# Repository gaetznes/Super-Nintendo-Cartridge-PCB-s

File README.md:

# Super-Nintendo-Cartridge-PCB-s

An assortment of boards I designed while learning how to use Kicad

SNES BASIC 27C160 + CIC (Untested), will update once tested.

SNES 2X 27C160 NOBATTERY (Untested), will update once tested.

SNES 2X 27C160 w BATTERY (Untested), will update once tested.

## Acknowledgements and Thanks goes to:

The Edge connector and edge cut and a fare amount of the net, were sourced from:

Mousebitelabs, https://github.com/MouseBiteLabs/Super-Nintendo-Cartridges/tree/main/Basic%20UV

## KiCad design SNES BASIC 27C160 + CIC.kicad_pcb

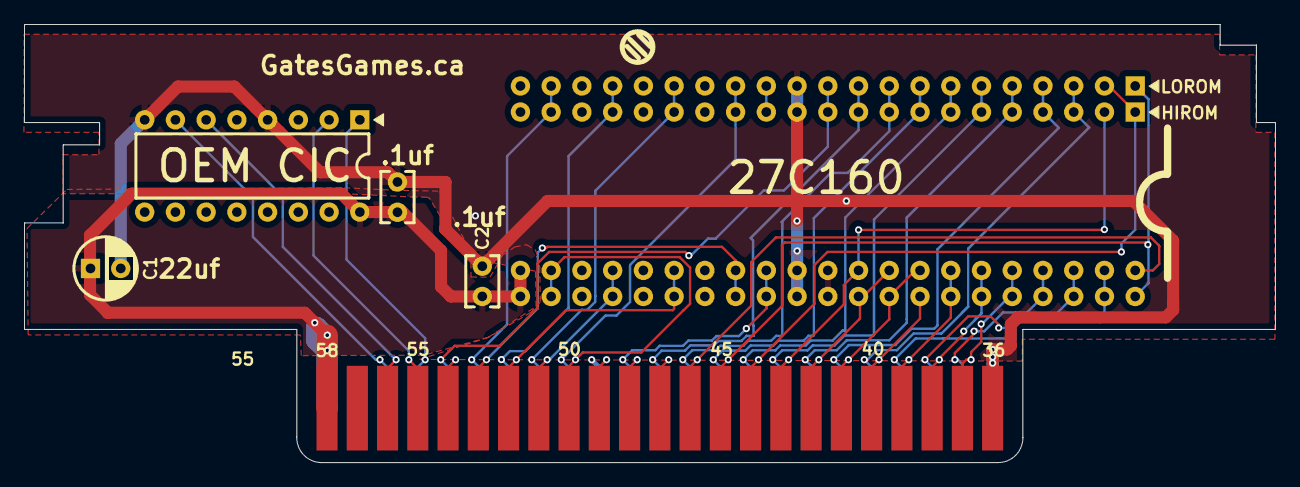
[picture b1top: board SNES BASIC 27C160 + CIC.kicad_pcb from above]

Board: 2 copper layers, 103.4 x 36.2 mm, 7 parts (0 on the bottom side), 38 nets.

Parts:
C1: 22u; CP_Radial_D5.0mm_P2.50mm
C2, C6L: 0.1u; C_THT
P1: SNES_Cartridge; Cart_Edge_SNES_Standard
U2C1: CIC; DIP-16_W7.62mm
U4H1, U4L1: 27C160; DIP-42_W15.24mm

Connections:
+5V: C1.1, C2.1, C6L.1, P1.27 (5V), P1.58 (5V), U2C1.16 (VDD), U4H1.22 (VCC), U4L1.22 (VCC)
/A_{0}: P1.17 (A0), U4H1.30 (D15), U4L1.30 (D15)
/A_{1}: P1.16 (A1), U4H1.10 (A0), U4L1.10 (A0)
/A_{2}: P1.15 (A2), U4H1.9 (A1), U4L1.9 (A1)
/A_{3}: P1.14 (A3), U4H1.8 (A2), U4L1.8 (A2)
/A_{4}: P1.13 (A4), U4H1.7 (A3), U4L1.7 (A3)
/A_{5}: P1.12 (A5), U4H1.6 (A4), U4L1.6 (A4)
/A_{6}: P1.11 (A6), U4H1.5 (A5), U4L1.5 (A5)
/A_{7}: P1.10 (A7), U4H1.4 (A6), U4L1.4 (A6)
/A_{8}: P1.9 (A8), U4H1.3 (A7), U4L1.3 (A7)
/A_{9}: P1.8 (A9), U4H1.41 (A8), U4L1.41 (A8)
/A_{10}: P1.7 (A10), U4H1.40 (A9), U4L1.40 (A9)
/A_{11}: P1.6 (A11), U4H1.39 (A10), U4L1.39 (A10)
/A_{12}: P1.37 (A12), U4H1.38 (A11), U4L1.38 (A11)
/A_{13}: P1.38 (A13), U4H1.37 (A12), U4L1.37 (A12)
/A_{14}: P1.39 (A14), U4H1.36 (A13), U4L1.36 (A13)
/A_{15}: P1.40 (A15), U4H1.35 (A14)
/BA_{0}: P1.41 (BA0), U4H1.34 (A15), U4L1.35 (A14)
/BA_{1}: P1.42 (BA1), U4H1.33 (A16), U4L1.34 (A15)
/BA_{2}: P1.43 (BA2), U4H1.2 (A17), U4L1.33 (A16)
/BA_{3}: P1.44 (BA3), U4H1.1 (A18), U4L1.2 (A17)
/BA_{4}: P1.45 (BA4), U4H1.42 (A19), U4L1.1 (A18)
/BA_{5}: P1.46 (BA5), U4L1.42 (A19)
/CIC.CLK: P1.56 (CIC_{CLK}), U2C1.6 (CLK)
/CIC.D_{0}: P1.24 (CIC_{D0}), U2C1.1 (D0)
/CIC.D_{1}: P1.55 (CIC_{D1}), U2C1.2 (D1)
/CIC.RST: P1.25 (CIC_{RST}), U2C1.7 (RST)
/D_{0}: P1.19 (D0), U4H1.14 (D0), U4L1.14 (D0)
/D_{1}: P1.20 (D1), U4H1.16 (D1), U4L1.16 (D1)
/D_{2}: P1.21 (D2), U4H1.18 (D2), U4L1.18 (D2)
/D_{3}: P1.22 (D3), U4H1.20 (D3), U4L1.20 (D3)
/D_{4}: P1.50 (D4), U4H1.23 (D4), U4L1.23 (D4)
/D_{5}: P1.51 (D5), U4H1.25 (D5), U4L1.25 (D5)
/D_{6}: P1.52 (D6), U4H1.27 (D6), U4L1.27 (D6)
/D_{7}: P1.53 (D7), U4H1.29 (D7), U4L1.29 (D7)
/ROM/ROM.~OE: U4H1.13 (~GVPP), U4L1.13 (~GVPP)
/~RD: P1.23 (~RD), U4H1.11 (~CE), U4L1.11 (~CE)
GND: C1.2, C2.2, C6L.2, P1.5 (GND), P1.36 (GND), U2C1.4 (KEY/LOCK), U2C1.8 (VSS), U4H1.12 (GND), U4H1.31 (GND), U4H1.32 (A20), U4L1.12 (GND), U4L1.31 (GND), U4L1.32 (A20)
